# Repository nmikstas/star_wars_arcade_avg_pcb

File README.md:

# star-wars-arcade-avg-pcb
The source files for the reproduction of the 1983 Star Sars Arcade vector generator PCB. The PCB is designed with Kicad. This project is now complete and verified working!

# Folder Structure
* BOM - Bill of materials for the vector generator PCB
* Gerbers -The gerber files for the vector generator PCB
* pcb - The Kicad design files for the vector generator PCB

# PCB Specifications
* Layers: 2
* Dimensions: 293mm X 525mm
* Different PCB Design: 1
* PCB Thickness: 1.6mm
* Surface Finish: HASL
* Castellated Holes: No
* Copper Weight: 1oz.

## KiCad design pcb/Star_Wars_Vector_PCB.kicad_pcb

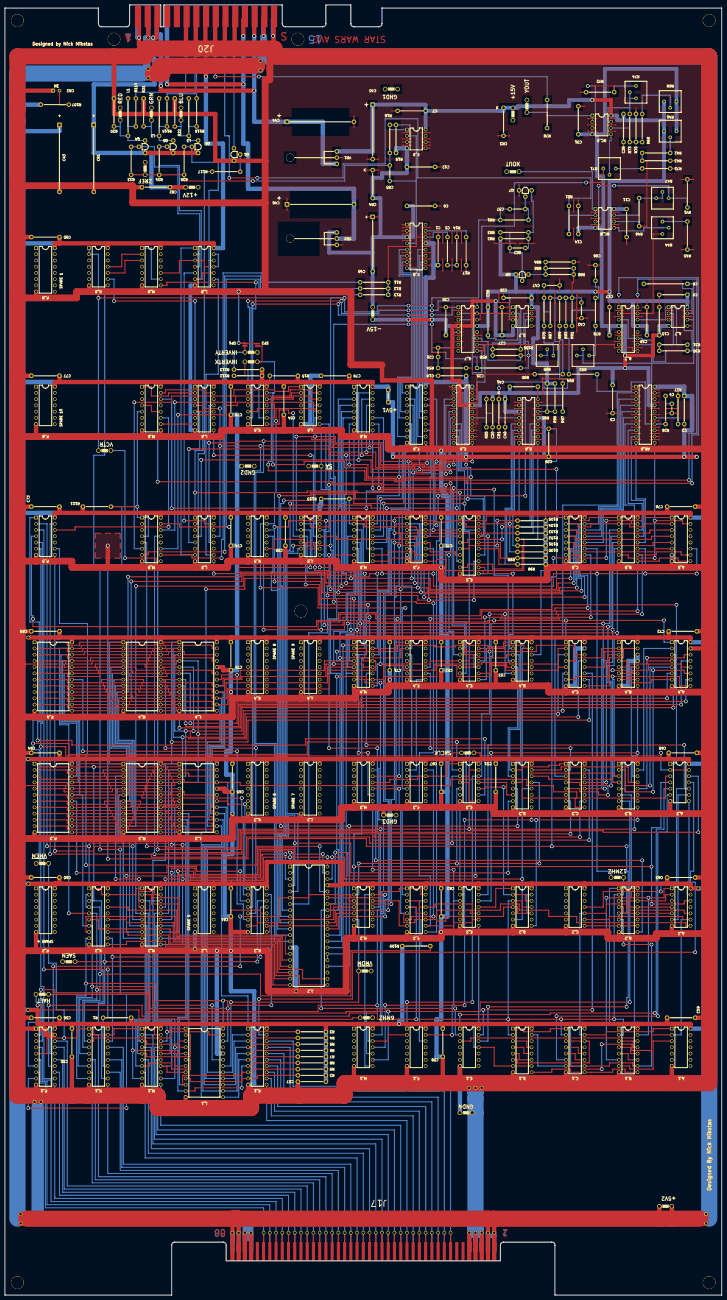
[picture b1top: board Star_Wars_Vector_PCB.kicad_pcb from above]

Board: 2 copper layers, 292.1 x 525.8 mm, 340 parts (0 on the bottom side), 330 nets.

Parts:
6MHZ1, 12MHZ1: TP; TEST_POINT
+5V1, +5V2, +12V1: TP; TEST_POINT
+15V1: TP1; TEST_POINT
-15V1: TP; TEST_POINT
AB_6: AM6012; DIP20
A_1: LS08; DIP14
A_2: LS20; DIP14
A_3: LS00; DIP14
A_4: LS157B; DIP16
A_5: LS194; DIP16
A_7: 082; DIP8
BC_8, BC_9: 082; DIP8
BLUE1: TP; TEST_POINT
B_1, B_2: LS161; DIP16
B_3: LS174A; DIP16
B_4: S129; DIP16
B_5: LS194; DIP16
B_7: LF13201; DIP16
C1, C2, C3, C6, C7, C9, C10, C11, C12, C14, C17, C18, C19, C20, C26, C27, C28, C31, C35, C36, C39, C40, C50, C51, C52, C53, C54, C55, C56, C57, C58, C59, C60, C61, C62, C63, C64, C65, C67, C68, C69, C70, C71, C72, C73, C74, C75, C76, C77, C78, C79, C80, C82: .1uF; GenericComp
C4, C21: .01uF; SmallCap
C5, C41: .01uF; GenericComp
C8, C25: .047uF; CapYellow
C37, C47, C66: 150pF; CapBrown
C38: 39pF; CapBrown
C42: 10pF; CapBrown
C43, C44, C46, C81: 100uF; LargeCap
C45, C48: 22uF; CapElec2
C83: 22pF; CapBrown
CR1: 1N914; GenericComp
CR2: LED
CR3, CR4: 1N100; GenericComp
C_1: LS161; DIP16
C_2: LS11; DIP14
C_3: LS175_A; DIP16
C_4: LS157A; DIP16
C_5: LS194; DIP16
D_1: LS161; DIP16
D_2: LS74; DIP14
D_3: LS42; DIP16
D_4: LS14; DIP14
D_6: DAC_8; DIP16
D_7: 082; DIP8
E_1, E_3: LS02; DIP14
E_2: LS32; DIP14
E_4: LS00; DIP14
E_5: LS273A; DIP20
E_6: AM6012; DIP20
E_7: LF13201; DIP16
F_1: LS27; DIP14
F_2: LS109; DIP16
F_3: S260; DIP14
F_4: LS86; DIP14
F_5: LS194; DIP16
F_6: LS273B; DIP20
F_8: DAC_8A; DIP16
F_9: 082; DIP8
GND1, GND2, GND3, GND4: TP; TEST_POINT
GREEN1: TP; TEST_POINT
HALT1: TP; TEST_POINT
H_1: LS74; DIP14
H_2: LS08; DIP14
H_3: LS02; DIP14
H_4: LS175; DIP16
H_5, H_6: LS194; DIP16
J17: Main_Connector; J17
J20: Edge_Connector_30_Pin; J20
J_2: AVG; DDIP40
J_3: Spare7; DIP18
J_4: Spare9; DIP18
J_5: LS32; DIP14
J_6: LS10; DIP14
K_1: LS245; DIP20
K_2: LS42; DIP16
K_3: Spare6; DIP18
K_4: Spare8; DIP18
K_5: LS74; DIP14
K_6: LS04; DIP14
L1, L2, L3: 1uH; Inductor1
L_1: 2732_A; DDIP24
L_2: Spare5; DIP16
L_3, L_4: 137211-001; DDIP24
L_5: LS175C; DIP16
L_6: LS175B; DIP16
L_8: 74LS07; DIP14
M_1, M_2: LS244_B; DIP20
M_3, M_4: 137211-001; DDIP24
M_5: LS175_A; DIP16
M_6: LS191A; DIP16
M_8: LS02; DIP14
N_1: LS244_A; DIP20
N_2: LS244_C; DIP20
N_8: LS164; DIP14
P_1: LS244; DIP20
P_2: Spare4; DIP16
P_3, P_4: 137211-001; DDIP24
P_5: LS04; DIP14
P_6: Spare10; DIP14
P_8: Spare1; DIP16
Q1, Q4, Q5, Q6, Q7: 2N3904; GenericTrans
Q8: 2N3906; GenericTrans
R1, R2, R3, R4, R5, R6, R7, R8, R9, R10, R83, R112, R113, R117: 10K; GenericComp
R11, R16: 12K; GenericComp
R12: 24K; GenericComp
R13: 47K; GenericComp
R14, R26, R27, R54, R55: 820; GenericComp
R15, R98, R99, R100, R101, R102, R103, R104, R105: 100K; GenericComp
R17: 6.2K; GenericComp
R20, R21, R22: 470; GenericComp
R23, R24, R25: 4.7k; GenericComp
R30, R31, R58, R85, R86, R89, R93, R95, R96, R106: 7.5K; GenericComp
R41, R44, R68, R71: 10K; PotBlue
R42, R69: 150K; GenericComp
R43, R70: 2.7K; GenericComp
R45, R72: 6.8K; GenericComp
R46, R73: 22K; GenericComp
R47, R74: 2K; PotBlk
R51, R78, R90, R94, R114, R115, R116: 100; GenericComp
R75, R76: 1.30K; GenericComp
R81: 15K; GenericComp
R82, R109, R110, R111: 1K; GenericComp
R84: 560; GenericComp
R87, R91: 6.19K; GenericComp
R88, R92: 200; PotBlk
R97: 3.9K; GenericComp
R107: 150; GenericComp
RED1: TP; TEST_POINT
RV1, RV2: VDR; GenericComp
Ref**: Val**; VIA_040
Ref**#2, Ref**#3, Ref**#4, Ref**#5, Ref**#6, Ref**#7, Ref**#8, Ref**#9, Ref**#10, Ref**#11, Ref**#12, Ref**#13, Ref**#14, Ref**#15, Ref**#16, Ref**#17, Ref**#18, Ref**#19, Ref**#20, Ref**#21, Ref**#22, Ref**#23, Ref**#24, Ref**#25, Ref**#26, Ref**#27, Ref**#28, Ref**#29, Ref**#30, Ref**#31, Ref**#32, Ref**#33, Ref**#34, Ref**#35, Ref**#36, Ref**#37, Ref**#38, Ref**#39, Ref**#40, Ref**#41, Ref**#42, Ref**#43, Ref**#44, Ref**#45, Ref**#46, Ref**#47, Ref**#48, Ref**#49, Ref**#50, Ref**#51, Ref**#52, Ref**#53, Ref**#54, Ref**#55, Ref**#56, Ref**#57, Ref**#58, Ref**#59, Ref**#60, Ref**#61: Val**; VIA_040
SACLK1: TP; TEST_POINT
SAEN1: TP; TEST_POINT
SP1, SP2: Split_Pad; SplitPad
VCTR1: TP; TEST_POINT
VR1: L7815_; VoltReg
VR2: L7915_; VoltReg
XOUT1: TP; TEST_POINT
YOUT1: TP; TEST_POINT
ZREF1: TP; TEST_POINT

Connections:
3MHZ: N_8.8, P_1.9
12MHZ: 12MHZ1.1, 12MHZ1.2, A_5.11, B_1.2, B_2.2, B_5.11, C_1.2, C_5.11, D_1.2, D_2.3, D_2.11, F_2.4, F_2.12, F_5.11, H_5.11, H_6.11, M_6.14, P_1.14
+5V: +5V1.1, +5V1.2, +5V2.1, +5V2.2, AB_6.20, A_1.14, A_2.14, A_3.14, A_4.16, A_5.16, B_1.16, B_2.16, B_3.16, B_4.16, B_5.16, C1.1, C2.1, C19.1, C39.1, C43.1, C50.1, C51.1, C52.1, C53.1, C54.1, C55.1, C56.1, C57.1, C58.1, C59.1, C60.1, C61.1, C62.1, C63.1, C64.1, C65.1, C67.1, C68.1, C69.1, C70.1, C71.1, C72.1, C73.1, C74.1, C75.1, C76.1, C77.1, C78.1, C79.1, C80.1, C_1.16, C_2.14, C_3.16, C_4.16, C_5.16, D_1.16, D_2.14, D_3.16, D_4.14, D_6.13, E_1.14, E_2.14, E_3.14, E_4.14, E_5.20, E_6.20, F_1.14, F_2.16, F_3.14, F_4.14, F_5.16, F_6.20, F_8.13, H_1.14, H_2.14, H_3.14, H_4.16, H_5.16, H_6.16, J17.1, J17.2, J17.3, J17.4, J17.83, J17.84, J17.85, J17.86, J20.2, J20.14, J20.B, J20.R, J_2.37, J_3.18, J_4.18, J_5.14, J_6.14, K_1.20, K_2.16, K_3.18, K_4.18, K_5.14, K_6.14, L_1.24, L_2.16, L_3.24, L_4.24, L_5.16, L_6.16, L_8.14, M_1.20, M_2.20, M_3.24, M_4.24, M_5.16, M_6.16, M_8.14, N_1.20, N_2.20, N_8.14, P_1.20, P_2.16, P_3.24, P_4.24, P_5.14, P_6.14, P_8.16, R1.1, R2.1, R3.1, R4.1, R5.1, R6.1, R7.1, R8.1, R9.1, R10.2, R107.1, R109.2, R110.2, R111.2, R112.1, R113.1, Ref**.1, Ref**#2.1, Ref**#5.1, Ref**#6.1, Ref**#47.1, Ref**#48.1, Ref**#49.1, Ref**#50.1, Ref**#51.1, Ref**#52.1, Ref**#54.1, Ref**#55.1, Ref**#56.1, Ref**#57.1, Ref**#58.1, Ref**#59.1, Ref**#60.1, Ref**#61.1
+12V: +12V1.1, +12V1.2, C81.1, C82.1, J20.C, Q4.3, Q5.3, Q6.3
+15V: +15V1.1, +15V1.2, A_7.8, BC_8.8, BC_9.8, B_7.13, C7.1, C9.2, C11.2, C18.1, C26.2, C28.2, C36.1, C45.1, CR3.1, D_7.8, E_7.13, F_9.8, Q8.1, R41.1, R68.1, R82.2, R95.1, R96.1, VR1.3
+22VDC: C44.1, J20.3, J20.P, VR1.1
-15V: -15V1.1, -15V1.2, AB_6.17, A_7.4, BC_8.4, BC_9.4, B_7.4, C3.2, C6.1, C10.2, C12.1, C14.2, C17.1, C20.2, C27.2, C31.2, C35.1, C40.1, C41.1, C48.2, CR4.2, D_6.3, D_7.4, E_6.17, E_7.4, F_8.3, F_9.4, R15.2, R41.3, R68.3, VR2.3
-22VDC: C46.2, J20.4, J20.N, VR2.2
AB0: J17.43, J17.44, M_1.6, Ref**#26.1
AB1: J17.35, J17.36, M_1.15, Ref**#30.1
AB2: J17.33, J17.34, M_1.13, Ref**#31.1
AB3: J17.31, J17.32, M_1.11, Ref**#38.1
AB4: J17.45, J17.46, M_1.8, Ref**#25.1
AB5: J17.37, J17.38, M_1.17, Ref**#29.1
AB6: J17.41, J17.42, M_1.4, Ref**#27.1
AB7: J17.39, J17.40, M_1.2, Ref**#28.1
AB8: J17.47, J17.48, N_1.17, Ref**#24.1
AB9: J17.49, J17.50, N_1.15, Ref**#23.1
AB10: J17.51, J17.52, N_1.13, Ref**#22.1
AB11: J17.53, J17.54, N_1.11, Ref**#21.1
AB12: J17.59, J17.60, N_1.8, Ref**#18.1
AB13: J17.55, J17.56, N_1.2, Ref**#20.1
AM0: A_4.13, L_1.8, L_3.8, L_4.8, M_1.14, M_2.14, M_3.8, M_4.8, P_3.8, P_4.8
AM1: A_4.10, L_1.7, L_3.7, L_4.7, M_1.5, M_2.5, M_3.7, M_4.7, P_3.7, P_4.7
AM2: A_4.6, L_1.6, L_3.6, L_4.6, M_1.7, M_2.7, M_3.6, M_4.6, P_3.6, P_4.6
AM3: A_4.3, L_1.5, L_3.5, L_4.5, M_1.9, M_2.9, M_3.5, M_4.5, P_3.5, P_4.5
AM4: C_4.6, L_1.4, L_3.4, L_4.4, M_1.12, M_2.12, M_3.4, M_4.4, P_3.4, P_4.4
AM5: C_4.3, L_1.3, L_3.3, L_4.3, M_1.3, M_2.3, M_3.3, M_4.3, P_3.3, P_4.3
AM6: C_4.13, L_1.2, L_3.2, L_4.2, M_1.16, M_2.16, M_3.2, M_4.2, P_3.2, P_4.2
AM7: C_4.10, L_1.1, L_3.1, L_4.1, M_1.18, M_2.18, M_3.1, M_4.1, P_3.1, P_4.1
AM8: L_1.23, L_3.23, L_4.23, M_3.23, M_4.23, N_1.3, N_2.3, P_3.23, P_4.23
AM9: L_1.22, L_3.22, L_4.22, M_3.22, M_4.22, N_1.5, N_2.5, P_3.22, P_4.22
AM10: L_1.19, L_3.19, L_4.19, M_3.19, M_4.19, N_1.7, N_2.7, P_3.19, P_4.19
AM11: K_2.15, L_1.21, N_1.9, N_2.9
AM12: K_2.14, N_1.12, N_2.14, SAEN1.1, SAEN1.2
AM13: K_2.13, N_1.18, N_2.12
AVG0: J_2.36, P_5.9
AVG1: J_2.39, M_2.15
AVG2: J_2.40, M_2.13
AVG3: J_2.1, M_2.11
AVG4: J_2.2, M_2.8
AVG5: J_2.3, M_2.17
AVG6: J_2.15, M_2.4
AVG7: J_2.16, M_2.2
AVG8: J_2.17, N_2.17
AVG9: J_2.18, N_2.15
AVG10: J_2.19, N_2.13
AVG11: J_2.20, N_2.11
AVG12: J_2.21, N_2.6
AVG13: J_2.22, N_2.8
BLANK: M_8.1, M_8.9
BLUE: J20.8, R116.2
CNTR: E_2.10, F_2.6, F_3.13
DVG0: A_5.6, C_5.6, F_5.6, H_6.6, K_1.9, L_1.9, L_3.9, L_4.9, M_3.9, M_4.9, P_3.9, P_4.9, R2.2
DVG1: A_5.5, C_5.5, F_5.5, H_6.5, K_1.8, L_1.10, L_3.10, L_4.10, M_3.10, M_4.10, P_3.10, P_4.10, R9.2
DVG2: A_5.4, C_5.4, F_5.4, H_6.4, K_1.7, L_1.11, L_3.11, L_4.11, M_3.11, M_4.11, P_3.11, P_4.11, R8.2
DVG3: A_5.3, C_5.3, F_5.3, H_6.3, K_1.6, L_1.13, L_3.13, L_4.13, M_3.13, M_4.13, P_3.13, P_4.13, R7.2
DVG4: B_5.6, C_3.4, H_4.13, H_5.6, K_1.5, L_1.14, L_3.14, L_4.14, M_3.14, M_4.14, P_3.14, P_4.14, R6.2
DVG5: B_5.5, C_3.13, H_4.5, H_5.5, K_1.4, L_1.15, L_3.15, L_4.15, M_3.15, M_4.15, P_3.15, P_4.15, R5.2
DVG6: B_5.4, C_3.5, H_4.12, H_5.4, K_1.3, L_1.16, L_3.16, L_4.16, M_3.16, M_4.16, P_3.16, P_4.16, R4.2
DVG7: B_5.3, C_3.12, H_4.4, H_5.3, K_1.2, L_1.17, L_3.17, L_4.17, M_3.17, M_4.17, P_3.17, P_4.17, R3.2
DVX3: AB_6.11, A_5.15, B_5.7
DVX4: AB_6.10, B_5.12
DVX5: AB_6.9, B_5.13
DVX6: AB_6.8, B_5.14
DVX7: AB_6.7, B_5.15, C_5.7
DVX8: AB_6.6, C_5.12
DVX9: AB_6.5, C_5.13
DVX10: AB_6.4, C_5.14
DVX11: AB_6.3, C_5.15, F_4.10
DVX12: C_3.2, F_4.9
DVY0: E_5.7, F_5.12, F_6.13, J_2.32
DVY1: E_5.4, F_5.13, F_6.14, J_2.31
DVY2: E_5.3, F_5.14, F_6.17, J_2.30
DVY3: E_5.13, E_6.11, F_5.15, F_6.18, H_5.7, J_2.7
DVY4: E_5.8, E_6.10, F_6.3, H_5.12, J_2.8
DVY5: E_5.18, E_6.9, F_6.4, H_5.13, J_2.9
DVY6: E_5.17, E_6.8, F_6.7, H_5.14, J_2.10
DVY7: E_5.14, E_6.7, F_6.8, H_5.15, H_6.7, J_2.11
DVY8: E_6.6, H_6.12, J_2.12, L_5.12, L_6.13
DVY9: E_6.5, H_6.13, J_2.13, L_5.13, L_6.4
DVY10: E_6.4, H_6.14, J_2.29, L_5.5, L_6.5, L_6.12
DVY11: E_6.3, F_4.2, H_6.15, J_2.28, L_5.4
DVY12: F_4.1, H_4.15, J_2.27, J_5.2
E1.5MHZ: J17.75, J17.76, P_1.8, Ref**#37.1
E3MHZ: J17.69, J17.70, P_1.11, Ref**#34.1
E6MHZ: J17.67, J17.68, P_1.13, Ref**#33.1
E12MHZ: J17.73, J17.74, P_1.6, Ref**#36.1
F0: A_4.14, B_3.12
F1: A_4.11, B_3.5
F2: A_4.5, B_3.2
F3: A_4.2, B_3.15
GND: AB_6.1, AB_6.12, AB_6.13, AB_6.19, A_1.7, A_2.7, A_3.7, A_4.8, A_4.15, A_5.7, A_5.8, A_7.3, A_7.5, B_1.8, B_2.8, B_3.8, B_4.8, B_4.13, B_4.14, B_5.8, B_7.5, C1.2, C2.2, C3.1, C4.1, C6.2, C7.2, C9.1, C10.1, C11.1, C12.2, C14.1, C17.2, C18.2, C19.2, C20.1, C21.1, C26.1, C27.1, C28.1, C31.1, C35.2, C36.2, C39.2, C40.2, C42.1, C43.2, C44.2, C45.2, C46.1, C47.1, C48.1, C50.2, C51.2, C52.2, C53.2, C54.2, C55.2, C56.2, C57.2, C58.2, C59.2, C60.2, C61.2, C62.2, C63.2, C64.2, C65.2, C66.1, C67.2, C68.2, C69.2, C70.2, C71.2, C72.2, C73.2, C74.2, C75.2, C76.2, C77.2, C78.2, C79.2, C80.2, C81.2, C82.2, CR1.2, CR2.1, CR3.2, CR4.1, C_1.8, C_2.7, C_3.8, C_4.8, C_4.15, C_5.8, D_1.8, D_2.7, D_3.8, D_4.7, D_6.2, D_7.3, D_7.5, E_1.7, E_2.7, E_3.7, E_4.7, E_5.10, E_6.1, E_6.12, E_6.13, E_6.19, E_7.5, F_1.7, F_2.8, F_3.7, F_4.7, F_5.7, F_5.8, F_6.10, F_8.1, F_8.2, F_9.3, F_9.5, F_9.6, GND1.1, GND1.2, GND2.1, GND2.2, GND3.1, GND3.2, GND4.1, GND4.2, H_1.7, H_2.7, H_3.7, H_4.8, H_5.8, H_6.8, J17.5, J17.6, J17.7, J17.8, J17.9, J17.10, J17.79, J17.80, J17.81, J17.82, J20.1, J20.15, J20.A, J20.F, J20.H, J20.J, J20.K, J20.L, J20.M, J20.S, J_2.14, J_3.9, J_4.9, J_5.7, J_6.7, K_1.10, K_2.8, K_2.12, K_3.9, K_4.9, K_5.7, K_6.7, L_1.12, L_1.20, L_2.8, L_3.12, L_3.20, L_4.12, L_4.20, L_5.8, L_6.8, L_8.7, M_1.10, M_2.10, M_3.12, M_3.20, M_4.12, M_4.20, M_5.8, M_6.8, M_6.9, M_8.7, N_1.10, N_2.10, N_8.7, P_1.1, P_1.10, P_1.19, P_2.8, P_3.12, P_3.20, P_4.12, P_4.20, P_5.7, P_6.7, P_8.8, Q1.1, Q7.1, R14.2, R17.1, R20.1, R21.1, R22.1, R27.1, R43.2, R45.1, R55.1, R70.2, R72.1, R84.1, R97.1, R98.2, R99.2, R100.2, R101.2, R102.1, R103.1, R104.1, R105.1, RV1.2, RV2.2, Ref**#3.1, Ref**#4.1, Ref**#7.1, Ref**#8.1, Ref**#9.1, Ref**#10.1, Ref**#11.1, Ref**#12.1, Ref**#13.1, Ref**#14.1, Ref**#15.1, Ref**#53.1, SP1.1, SP2.1, VR1.2, VR2.1
GO: D_1.7, D_1.10, E_1.11, E_2.8
GREEN: J20.7, R115.2
HALT: B_3.6, HALT1.1, HALT1.2, H_1.9, P_1.2
HALT*: B_3.7, E_1.12
NORM: H_3.12, J_6.9, K_5.9
unnamed: 6MHZ1.1, 6MHZ1.2, P_1.7
unnamed: AB_6.15, R27.2
unnamed: A_1.1, A_2.10, C_1.15, C_2.10
unnamed: A_1.2, A_2.9, C_1.7, C_2.9, D_1.15
unnamed: A_1.3, B_1.7
unnamed: A_2.1, B_1.15, C_2.11
unnamed: A_2.2, B_1.6, B_2.14
unnamed: A_2.4, B_2.3, B_2.13
unnamed: A_2.5, B_2.4, B_2.12
unnamed: A_2.6, A_3.9
unnamed: A_2.13, A_3.8
unnamed: A_3.1, P_5.4
unnamed: A_3.5, E_1.1
unnamed: A_3.6, C_1.6
unnamed: A_4.4, B_4.4
unnamed: A_4.7, B_4.7
unnamed: A_4.9, B_4.6
unnamed: A_4.12, B_4.5
unnamed: A_5.9, B_5.9, D_4.6
unnamed: A_5.10, B_5.10, E_4.8
unnamed: A_7.1, B_7.14, R31.1
unnamed: A_7.2, R30.1, R31.2
unnamed: A_7.7, B_7.3, B_7.11, C8.1, R30.2
unnamed: BC_8.1, BC_8.2, R51.2, XOUT1.1, XOUT1.2
unnamed: BC_8.3, R47.3, RV1.1
unnamed: BC_8.5, R44.2
unnamed: BC_8.6, R42.1, R43.1, R46.2
unnamed: BC_8.7, R46.1, R47.1, R47.2
unnamed: BC_9.1, BC_9.2, R78.2, YOUT1.1, YOUT1.2
unnamed: BC_9.3, R74.3, RV2.1
unnamed: BC_9.5, R71.2
unnamed: BC_9.6, R69.1, R70.1, R73.2
unnamed: BC_9.7, R73.1, R74.1, R74.2
unnamed: BLUE1.1, BLUE1.2, L3.2, Q6.1, R22.2
unnamed: B_1.9, B_2.9, C_1.9, D_1.9, H_3.13
unnamed: B_1.5, B_1.11
unnamed: B_1.4, B_1.12
unnamed: B_1.3, B_1.13
unnamed: B_1.14, E_1.3
unnamed: B_2.7, B_2.10, C_2.8
unnamed: B_3.4, B_4.11, D_3.14
unnamed: B_3.9, D_2.8
unnamed: B_3.13, B_4.12, D_3.15
unnamed: B_3.14, B_4.9, E_2.12
unnamed: B_4.1, C_4.12
unnamed: B_4.2, C_4.4
unnamed: B_4.3, C_4.7
unnamed: B_4.15, C_4.9
unnamed: B_7.1, K_6.12
unnamed: B_7.2, B_7.15, R44.1
unnamed: B_7.16, K_6.13, R112.2, SP2.2
unnamed: C4.2, R26.2
unnamed: C5.1, F_8.14, R11.1, R12.1, R13.1
unnamed: C5.2, R14.1
unnamed: C21.2, R54.2
unnamed: C25.1, D_7.7, E_7.3, E_7.11, R58.2
unnamed: C37.1, Q7.2, R81.1
unnamed: C38.1, Q8.2, R83.1
unnamed: C38.2, Q7.3, R82.1, R83.2
unnamed: C41.2, D_6.16
unnamed: C42.2, CR1.1, D_6.4, R85.1, R86.1, R87.2, R89.2, R91.2, R93.2
unnamed: C47.2, R75.2, R87.1
unnamed: C66.2, R76.2, R91.1
unnamed: C83.2, F_8.4, F_9.2, R15.1, R16.2
unnamed: CR2.2, R107.2
unnamed: C_1.5, C_1.11
unnamed: C_1.4, C_1.12
unnamed: C_1.3, C_1.13
unnamed: C_1.14, D_1.6
unnamed: C_4.11, E_1.13
unnamed: C_5.9, D_4.12
unnamed: C_5.10, E_4.11
unnamed: D_1.5, D_1.11
unnamed: D_1.4, D_1.12
unnamed: D_1.3, D_1.13
unnamed: D_2.1, E_2.11
unnamed: D_2.2, D_2.12, E_3.10
unnamed: D_4.2, F_5.9, H_5.9
unnamed: D_4.4, H_6.9
unnamed: D_6.5, E_5.15, R98.1
unnamed: D_6.6, E_5.16, R99.1
unnamed: D_6.7, E_5.19, R100.1
unnamed: D_6.8, E_5.9, R101.1
unnamed: D_6.9, E_5.12, R102.2
unnamed: D_6.10, E_5.2, R103.2
unnamed: D_6.11, E_5.5, R104.2
unnamed: D_6.12, E_5.6, R105.2
unnamed: D_6.14, R95.2, R96.2
unnamed: D_6.15, R97.2
unnamed: D_7.1, E_7.14, R106.1
unnamed: D_7.2, R58.1, R106.2
unnamed: E_2.3, F_1.13, H_3.8
unnamed: E_3.2, M_6.4, M_6.12
unnamed: E_3.4, E_3.8
unnamed: E_3.3, E_3.13, P_5.13
unnamed: E_4.3, F_5.10, H_5.10
unnamed: E_4.6, H_6.10
unnamed: E_6.15, R55.2
unnamed: E_7.1, K_6.2
unnamed: E_7.2, E_7.15, R71.1
unnamed: E_7.16, K_6.1, R113.2, SP1.2
unnamed: F_1.12, F_2.14
unnamed: F_2.2, H_3.10
unnamed: F_2.7, H_2.12
unnamed: F_3.1, F_4.3
unnamed: F_3.2, F_4.8
unnamed: F_3.5, J_6.10, K_5.13
unnamed: F_6.2, F_8.8
unnamed: F_6.5, F_8.7
unnamed: F_6.6, F_8.6
unnamed: F_6.9, F_8.5
unnamed: F_6.12, F_8.12
unnamed: F_6.15, F_8.11
unnamed: F_6.16, F_8.10
unnamed: F_6.19, F_8.9
unnamed: F_8.15, R17.2
unnamed: GREEN1.1, GREEN1.2, L2.2, Q5.1, R21.2
unnamed: H_2.3, J_2.35
unnamed: H_2.4, K_2.7
unnamed: H_2.5, K_2.9
unnamed: J_2.5, J_5.6
unnamed: J_5.1, J_5.8, J_5.12
unnamed: J_6.1, M_5.6
unnamed: J_6.2, M_5.11
unnamed: J_6.12, K_6.5
unnamed: J_6.13, M_5.14
unnamed: L1.1, R114.1
unnamed: L1.2, Q4.1, R20.2, RED1.1, RED1.2
unnamed: L2.1, R115.1
unnamed: L3.1, R116.1
unnamed: L_5.2, R117.1
unnamed: L_5.7, L_8.1
unnamed: L_5.10, L_8.9
unnamed: L_5.15, L_8.5
unnamed: L_6.2, M_6.1
unnamed: L_6.7, M_6.10
unnamed: L_6.15, M_6.15
unnamed: L_8.2, L_8.4, Q4.2, R23.2
unnamed: L_8.6, L_8.10, Q5.2, R24.2
unnamed: L_8.3, L_8.11, L_8.13, M_8.10
unnamed: L_8.8, L_8.12, Q6.2, R25.2
unnamed: M_2.6, P_5.8
unnamed: M_5.7, R12.2
unnamed: M_5.10, R11.2
unnamed: M_5.15, R13.2
unnamed: M_6.11, P_5.12
unnamed: M_8.2, N_8.11
unnamed: M_8.3, N_8.10
unnamed: N_1.14, P_5.3, R1.2
unnamed: Q1.2, R117.2
unnamed: Q8.3, R84.2, R85.2, R86.2
unnamed: R41.2, R42.2
unnamed: R44.3, R45.2
unnamed: R68.2, R69.2
unnamed: R71.3, R72.2
unnamed: R75.1, R88.3
unnamed: R76.1, R92.3
unnamed: R89.1, R90.2
unnamed: R93.1, R94.2
OP0: C_4.5, F_1.2, H_1.12, H_4.7
OP1: C_4.2, E_1.2, H_4.10, J_2.33
OP2: C_4.14, E_3.12, F_1.1, H_4.2, J_5.10
P1: D_2.4, D_2.10, D_2.13, F_2.5, F_2.11, K_5.10, N_1.4, N_2.2, N_2.4, R109.1
P2: A_5.2, B_5.2, C_5.2, F_5.2, H_4.1, H_5.2, H_6.1, H_6.2, R110.1
P3: B_1.10, B_2.5, B_2.6, C_1.1, C_1.10, D_1.1, F_6.1, M_5.1, M_5.4, M_6.5, R111.1
PD0: J17.29, J17.30, K_1.11, Ref**#39.1
PD1: J17.27, J17.28, K_1.12, Ref**#40.1
PD2: J17.25, J17.26, K_1.13, Ref**#41.1
PD3: J17.23, J17.24, K_1.14, Ref**#42.1
PD4: J17.21, J17.22, K_1.15, Ref**#43.1
PD5: J17.19, J17.20, K_1.16, Ref**#44.1
PD6: J17.17, J17.18, K_1.17, Ref**#45.1
PD7: J17.15, J17.16, K_1.18, Ref**#46.1
R/~WB: J17.57, J17.58, N_1.6, Ref**#19.1
RED: J20.6, R114.2
SA: A_4.1, C_4.1, E_2.13, J_5.4, K_6.8
SCALE: E_3.1, F_3.12, H_3.11
SPARE: J20.11, Q1.3
ST2: B_3.3, B_4.10, D_3.13, E_3.5, H_2.2
ST3: D_2.6, D_3.12, J_2.38
VCTR: C37.2, E_2.9, F_2.10, F_3.3, M_5.9, N_8.1, N_8.2, R81.2, VCTR1.1, VCTR1.2
VGCLK: A_3.2, A_3.13, E_2.1, P_1.12, P_5.5, SACLK1.1, SACLK1.2
VGHALT: J17.61, J17.62, P_1.18, Ref**#17.1
VMEM: A_3.12, M_2.1, M_2.19, N_2.1, N_2.19, P_5.2
XBIP: AB_6.18, A_7.6, B_7.10, C8.2, R92.1, R92.2
XREF: AB_6.14, R26.1, R94.1
X_OUT: J20.10, R51.1
YBIP: C25.2, D_7.6, E_6.18, E_7.10, R88.1, R88.2
YREF: E_6.14, R54.1, R90.1
Y_OUT: J20.9, R78.1
Z0: C_3.15, M_5.13
Z1: C_3.7, M_5.5
Z2: C_3.10, M_5.12
ZBLANK: K_6.6, M_8.8
ZREF: C83.1, F_9.1, R16.1, R23.1, R24.1, R25.1, ZREF1.1, ZREF1.2
~1.5MHZ: E_3.9, P_5.6
~BUFFEN: A_3.11, K_1.19
~CENTER: B_7.9, E_7.9, H_2.11
~DVX12: AB_6.2, C_3.3
~DVY12: E_6.2, H_4.14, J_5.13
~ENORM: E_4.2, E_4.5, E_4.10, E_4.12, J_6.8
~EVGGO: J17.71, J17.72, P_1.4, Ref**#35.1
~EVGRST: J17.63, J17.64, P_1.17, Ref**#16.1
~EVMEM: J17.65, J17.66, P_1.15, Ref**#32.1
~HALT: F_2.1, F_2.15, H_1.8, H_2.13
~LATCH0: D_3.1, D_4.1, E_4.1
~LATCH1: A_5.1, B_5.1, C_3.1, C_5.1, D_3.2, D_4.3, E_4.4, F_5.1, H_4.9, H_5.1
~LATCH2: D_3.3, D_4.5, E_4.9
~LATCH3: C_3.9, D_3.4, D_4.13, E_4.13
~OP0: H_4.6, J_2.25, J_2.26, K_5.12
~OP1: A_3.10, B_1.1, B_2.1, H_4.11
~OP2: H_3.9, H_4.3, J_5.5
~SA: A_2.12, A_3.4, H_2.1, J_6.11, K_6.9, R10.1
~SCALELD: E_5.11, J_5.11, L_6.9
~STATCLK: F_6.11, J_5.3, L_5.9
~STOP: A_2.8, F_2.3, F_2.13
~STROBE0: D_3.5, J_2.24, K_5.11
~STROBE1: D_3.6, E_3.11, J_2.34
~STROBE2: D_3.7, J_2.4, J_5.9
~STROBE3: D_3.9, E_2.2, H_1.11
~VCTR: D_6.1, F_2.9
~VGGO: H_1.13, J_2.6, P_1.16
~VGRST: B_3.1, E_5.1, H_1.10, L_5.1, L_6.1, N_8.9, P_1.3
~VMEM: E_3.6, M_1.1, M_1.19, N_1.1, N_1.19, P_1.5, P_5.1
~VRAM0: K_2.1, L_3.18
~VRAM1: K_2.2, M_3.18
~VRAM2: K_2.3, P_3.18
~VRAM3: K_2.4, L_4.18
~VRAM4: K_2.5, M_4.18
~VRAM5: K_2.6, P_4.18
~VROM: H_2.6, L_1.18
~VW: A_3.3, K_1.1, L_3.21, L_4.21, M_3.21, M_4.21, P_3.21, P_4.21

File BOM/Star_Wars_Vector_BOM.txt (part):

Reference                                   Quantity        Value           Part#

A_2                                         1               "LS20"          Jameco 47095
A_3 E_4                                     2               "LS00"          Jameco 46252
A_4 C_4                                     2               "LS157"         Jameco 46771
A_7 BC_8 D_7 BC_9 F_9                       5               "082"           Jamec0 33241
B_3                                         1               "LS174"         Jameco 46931
B_4                                         1               "S129"          Alan-1 state machine ROM
B_7 E_7                                     2               "LF13201"       Digikey DG201BDJ-E3-ND
C_2                                         1               "LS11"          Jameco 46439
C_5 B_5 A_5 F_5 H_5 H_6                     6               "LS194"         Jameco 47052
D_1 C_1 B_1 B_2                             4               "LS161"         Jameco 46818
D_4                                         1               "LS14"          Jameco 46640
D_6 F_8                                     2               "DAC-08"        Digikey DAC0800LCN/NOPB-ND
E_3 E_1 H_3 M_8                             4               "LS02"          Jameco 46287
E_5 F_6                                     2               "LS273"         Jameco 47386
E_6 AB_6                                    2               "AM6012"        Digikey DAC312HPZ-ND
F_1                                         1               "LS27"          Jameco 47378
F_2                                         1               "LS109"         Jameco 46421
F_3                                         1               "S260"          Jameco 64725
F_4                                         1               "LS86"          Jameco 48098
H_2 A_1                                     2               "LS08"          Jamec0 46375
H_4 L_5 L_6 M_5 C_3                         5               "LS175"         Jameco 46957
J_2                                         1               "AVG"           Alan-1 AVG
J_5 E_2                                     2               "LS32"          Jameco 47466
J_6                                         1               "LS10"          Jameco 46404
K_1                                         1               "LS245"         Jameco 47212
K_2 D_3                                     2               "LS42"          Jameco 47773
K_5 D_2 H_1                                 3               "LS74"          Jameco 48004
L_1                                         1               "2732_A"        Jameco 40125
L_3 M_3 P_3 L_4 M_4 P_4                     6               "137211-001"    Jameco 2302575                                          
L_8                                         1               "74LS07"        Jameco 46367
M_1 M_2 N_1 N_2 P_1                         5               "LS244"         Jameco 47183
M_6                                         1               "LS191"         Jameco 47001
N_8                                         1               "LS164"         Jameco 46851
P_5 K_6                                     2               "LS04"          Jameco 46316

C37 C47 C66                                 3               "150pF"         Digikey 399-4213-ND‎
C38                                         1               "39pF"          Digikey 399-4238-ND‎
C4 C21                                      2               ".01uF"         Digikey 399-14040-1-ND‎
C41 C5                                      2               ".01uF"         Digikey 399-4452-1-ND‎
C42                                         1               "10pF"          Digikey 399-14082-ND‎
C43 C44 C46 C81                             4               "100uF"         Digikey 1572-1050-ND‎
C45 C48                                     2               "22uF"          Digikey 1572-1394-ND‎
C8 C25                                      2               ".047uF"        Digikey BC3089-ND‎
C83                                         1               "22pF"          Digikey 1270PH-ND‎
C1 C2 C3 C6 C7 C9 C10 C11 C12 C14           53              ".1uF"          Digikey 399-4454-1-ND
C17 C18 C19 C20 C26 C27 C28 C31 C35 C36
C39 C40 C50 C51 C52 C53 C54 C55 C56 C57
C58 C59 C60 C61 C62 C63 C64 C65 C67 C68
C69 C70 C71 C72 C73 C74 C75 C76 C77 C78
C79 C80 C82  

CR1                                         1               "1N914"         Digikey 1N914FS-ND
CR2                                         1               "LED"           Digikey VAOL-5701SBY4-ND
CR3 CR4                                     2               "1N400"         Digikey 1N4005GP-E3/54

L1 L2 L3                                    3               "1uH"           Digikey M10137-ND‎

Q4 Q5 Q6 Q1 Q7                              5               "2N3904"        Digikey 2N3904-APCT-ND‎
Q8                                          1               "2N3906"        Digikey 2N3906-APCT-ND‎

R44 R41 R71 R68                             4               "10K POT"       Digikey 3386P-103-ND‎
R47 R74                                     2               "2K  POT"       Digikey 3386P-202-ND‎
R88 R92                                     2               "200 POT"       Digikey 3386P-201LF-ND
R26 R27 R54 R55 R14                         5               "820"           Digikey 820QBK-ND‎
R84                                         1               "560"           Digikey 560QBK-ND‎
R87 R91                                     2               "6.19K"         Digikey 6.19KXBK-ND‎
R75 R76                                     2               "1.30K"         Digikey 1.30KXBK-ND‎
R11 R16                                     2               "12K"           Digikey 12KQBK-ND‎
R12                                         1               "24K"           Digikey CF14JT24K0CT-ND‎
R13                                         1               "47K"           Digikey 47KQBK-ND‎
R17                                         1               "6.2K"          Digikey 6.2KQBK-ND‎
R20 R21 R22                                 3               "470"           Digikey 470QBK-ND‎
R23 R24 R25                                 3               "4.7k"          Digikey 4.7KQBK-ND‎
R109 R110 R111 R82 R107                     5               "1K"            Digikey CFR-25JB-52-1K
R42 R69                                     2               "150K"          Digikey 150KQBK-ND‎
R43 R70                                     2               "2.7K"          Digikey S2.7KHCT-ND
R45 R72                                     2               "6.8K"          Digikey CFR-25JB-52-6K8
R46 R73                                     2               "22K"           Digikey FMP100JR-52-22K
R81                                         1               "15K"           Digikey FMP100JR-52-15K
R97                                         1               "3.9K"          Digikey CFR-25JB-52-3K9
R51 R78 R114 R115 R116 R90 R94              7               "100"           Digikey CFR-25JB-52-100R
R30 R31 R58 R106 R95 R96 R85 R86 R89 R93    10              "7.5K"          Digikey 7.50KXBK-ND‎
R98 R99 R100 R101 R102 R103 R104 R105 R15   9               "100K"          Digikey CF14JT100KCT-ND
R1 R2 R3 R4 R5 R6 R7 R8 R9 R10              14              "10K"           Digikey CFR-25JB-52-10K
R83 R112 R113 R117

RV1 RV2                                     2               "VDR"           Alan-1 varistor

VR1                                         1               "L7815_"        Digikey 296-21624-5-ND‎
VR2                                         1               "L7915_"        Digikey 497-7295-5-ND‎

Plastic tabs                                2               "Tabs"          Digikey RPC1553-ND

+15V1 -15V1 +12V1 ~VMEM1 SACLK1 ~VROM1      26              "TP"            Digikey WM6456-ND
~SA1 HALT1 ~INVERTX1 XOUT1 ~INVERTY1
YOUT1 ZREF1 RED1 GREEN1 BLUE1 +5V2
+5V1 GND4 GND3 GND2 GND1 SAEN1 VCTR1
12MHZ1 6MHZ1

Sockets:
8  pin: 5           Jameco 112206
14 pin: 24          Jameco 112214
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
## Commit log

2020-11-29 Added all design files
2020-11-29 Updated readme file
2021-03-24 Updated PCB design and added BOM
2021-04-13 Fixed errors on the schematic
2021-04-14 Updated the gerbers
2021-04-14 Updated the readme file
2021-04-17 Fixed the solder mask on J20
2022-02-18 Updated test points on pcb and readme file
